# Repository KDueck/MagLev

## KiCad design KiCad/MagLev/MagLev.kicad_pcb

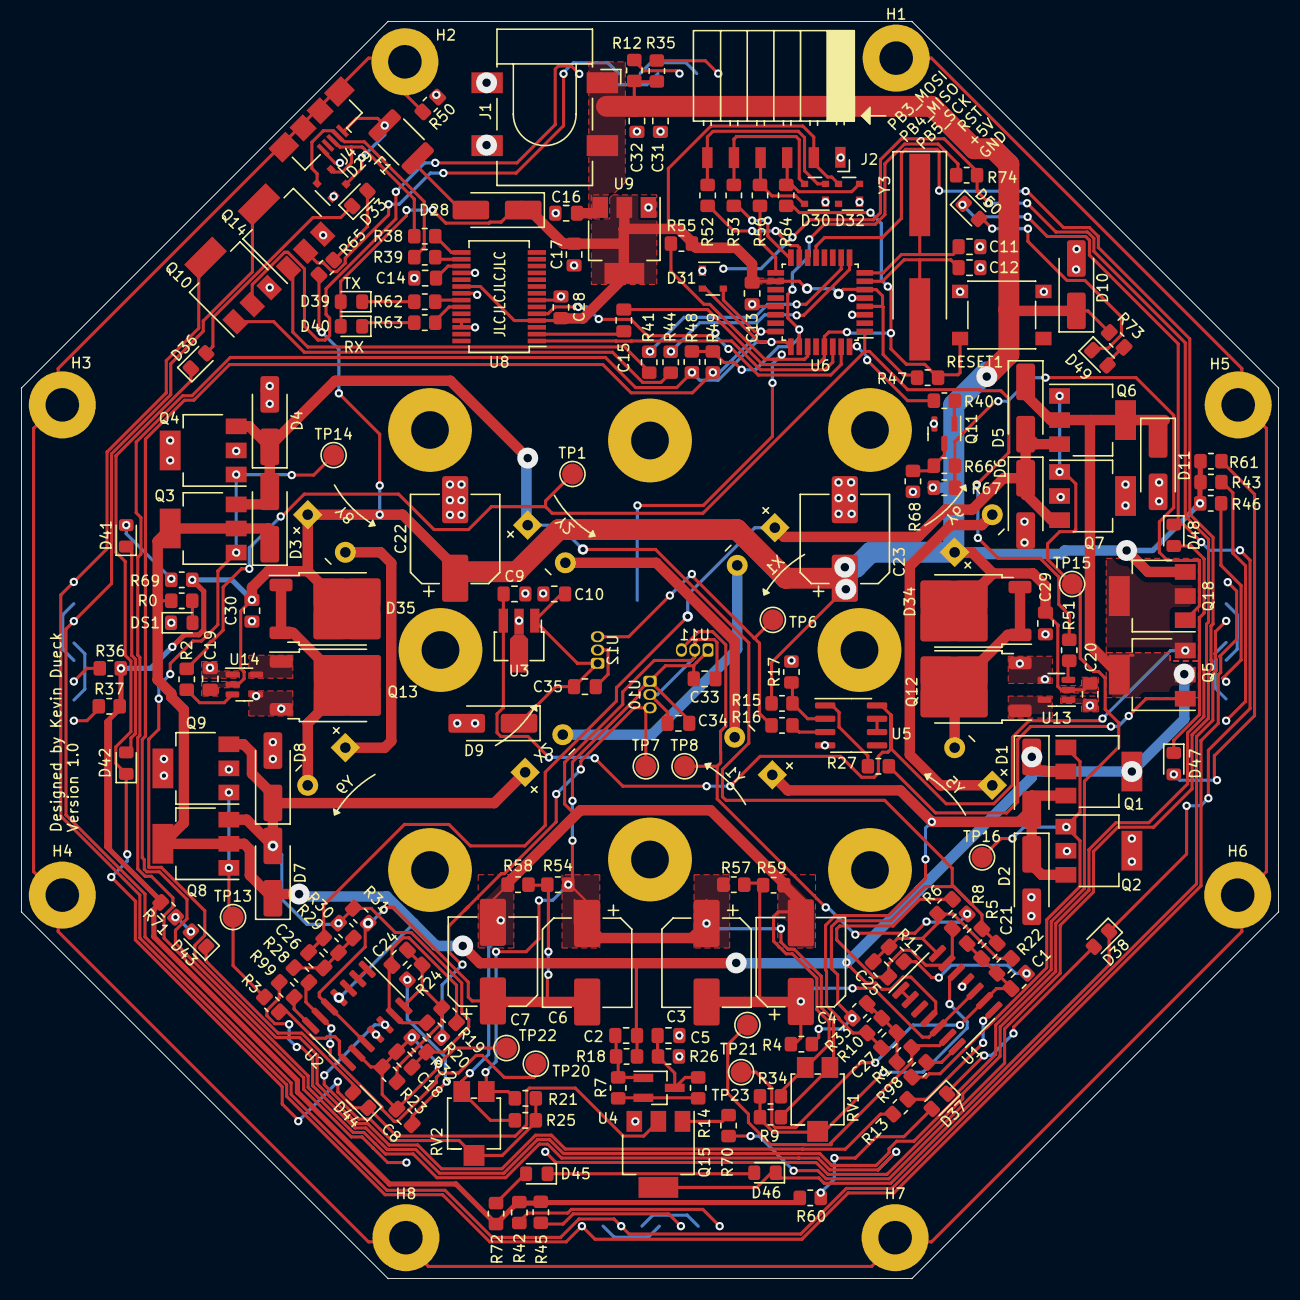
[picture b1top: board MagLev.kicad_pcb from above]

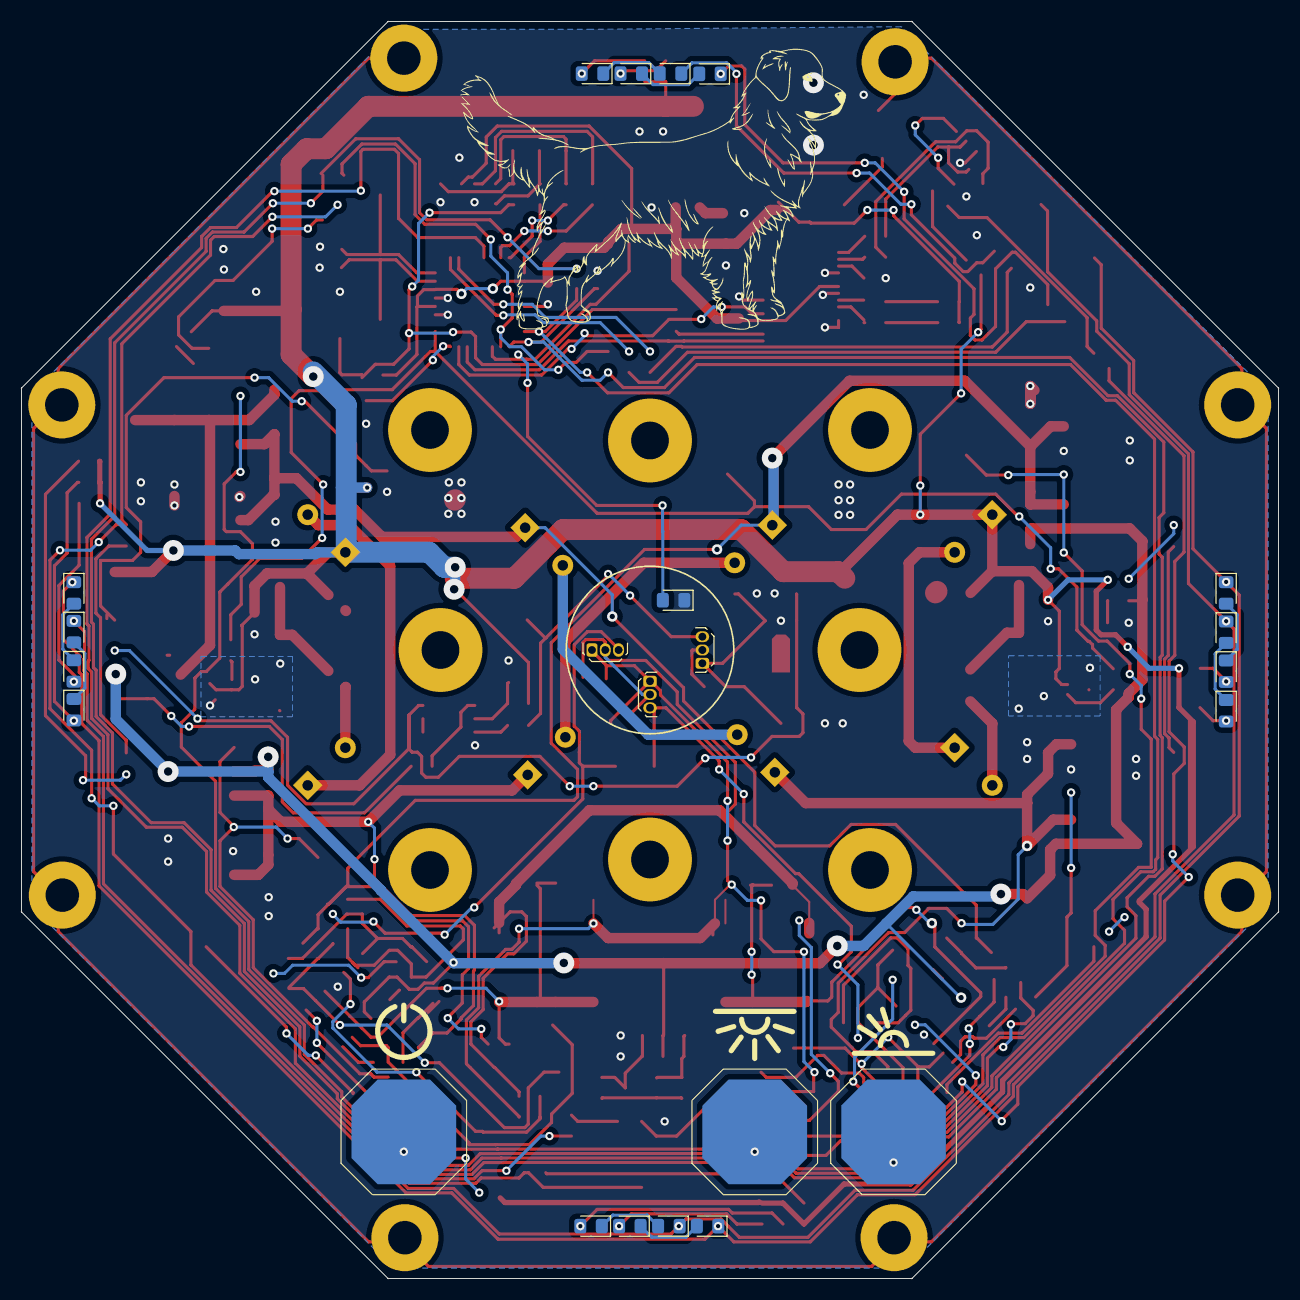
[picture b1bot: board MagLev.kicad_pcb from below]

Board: 2 copper layers, 120.0 x 120.0 mm, 232 parts (31 on the bottom side), 134 nets.

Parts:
C1, C8: 1uF; C_0805_2012Metric_Pad1.18x1.45mm_HandSolder
C2, C5: .1uF; C_0805_2012Metric_Pad1.18x1.45mm_HandSolder
C3, C4, C6, C7, C22, C23: 220uF; CP_Elec_8x10_HandSolder
C9: 0.33uF; C_0805_2012Metric_Pad1.18x1.45mm_HandSolder
C10: 0.01uF; C_0805_2012Metric_Pad1.18x1.45mm_HandSolder
C11, C12: 22pF; C_0805_2012Metric_Pad1.18x1.45mm_HandSolder
C13, C19, C20, C28, C32, C33, C34, C35: 0.1uF; C_0805_2012Metric_Pad1.18x1.45mm_HandSolder
C14, C15: 100nF; C_0805_2012Metric_Pad1.18x1.45mm_HandSolder
C16, C17: 10uF; C_0805_2012Metric_Pad1.18x1.45mm_HandSolder
C18, C21: 4.7nF; C_0805_2012Metric_Pad1.18x1.45mm_HandSolder
C24, C25: 470pF; C_0805_2012Metric_Pad1.18x1.45mm_HandSolder
C26, C27: 33nF; C_0805_2012Metric_Pad1.18x1.45mm_HandSolder
C29, C30, C31: 4.7uF; C_0805_2012Metric_Pad1.18x1.45mm_HandSolder
D1, D2, D3, D4, D5, D6, D7, D8: B140; D_SMA_Handsoldering
D9: SMAJ5.0A; D_SMA_Handsoldering
D10, D11: SMAJ12A; D_SMA_Handsoldering
D12, D13, D14, D15, D16, D17, D18, D19: WH; LED_0805_2012Metric_Pad1.15x1.40mm_HandSolder
D20, D21, D22, D23, D24, D25, D26, D27: UV; LED_0805_2012Metric_Pad1.15x1.40mm_HandSolder
D28: D; D_SMA_Handsoldering
D29, D30, D31, D32: SP0503BAHT; SOT-143
D33, D36, D37, D38, D41, D42, D43, D44, D45, D46, D47, D48, D49, D50: WRM; LED_0805_2012Metric_Pad1.15x1.40mm_HandSolder
D34, D35: MBRD1060; TO-252-Schottkey
D39: GREEN; LED_0805_2012Metric_Pad1.15x1.40mm_HandSolder
D40: Red; LED_0805_2012Metric_Pad1.15x1.40mm_HandSolder
DS1: GREEN; LED_0805_2012Metric_Pad1.15x1.40mm_HandSolder
F1: MF-MSMF050-2; Fuse_1812_4532Metric_Pad1.30x3.40mm_HandSolder
H1, H2, H3, H4, H5, H6, H7, H8: MountingHole_Pad; MountingHole_3.2mm_M3_Pad
J1: FC681465S; BarrelJack_CLIFF_FC681465S_SMT_Horizontal_No_Holes
J2: Programming header; PinSocket_1x06_P2.54mm_Horizontal_SM
J4: USB_B_Micro; USB_Micro-B_Amphenol_10104110_Horizontal_Overhang
PB1, PB2, PB3: Capacitive_Touch_Pad
Q1, Q3, Q6, Q8, Q10, Q14, Q15: ZX5T851GTA; SOT-223-3_TabPin2_BJT
Q2, Q4, Q5, Q7, Q9, Q18: ZX5T1951GTA; SOT-223-3_TabPin2_BJT
Q11: MMBT3904; SOT-23
Q12, Q13: AOD442G; TO-252-2
Q16: TEMT7000X01; LED_0805_2012Metric_Pad1.15x1.40mm_HandSolder
R0: 1K; R_0805_2012Metric_Pad1.20x1.40mm_HandSolder
R1, R28: 430k; R_0805_2012Metric_Pad1.20x1.40mm_HandSolder
R2, R9, R11, R21, R24, R25, R27, R34, R38, R39, R40, R41, R44, R47, R51, R52, R53, R54, R56, R57, R58, R59, R64, R66, R70: 1k; R_0805_2012Metric_Pad1.20x1.40mm_HandSolder
R3, R13, R98, R99: 51; R_0805_2012Metric_Pad1.20x1.40mm_HandSolder
R4, R31: 330k; R_0805_2012Metric_Pad1.20x1.40mm_HandSolder
R5, R8, R20, R32, R67: 10k; R_0805_2012Metric_Pad1.20x1.40mm_HandSolder
R6, R19: 130k; R_0805_2012Metric_Pad1.20x1.40mm_HandSolder
R7, R14, R16, R17: 5.1k; R_0805_2012Metric_Pad1.20x1.40mm_HandSolder
R10, R29: 1.5k; R_0805_2012Metric_Pad1.20x1.40mm_HandSolder
R12, R35, R36, R37, R42, R43, R45, R46, R60, R61, R65, R69, R71, R72, R73: 270; R_0805_2012Metric_Pad1.20x1.40mm_HandSolder
R15: 20k; R_0805_2012Metric_Pad1.20x1.40mm_HandSolder
R18, R26: 180; R_0805_2012Metric_Pad1.20x1.40mm_HandSolder
R22, R23: 3.3k; R_0805_2012Metric_Pad1.20x1.40mm_HandSolder
R30, R33: 1.2k; R_0805_2012Metric_Pad1.20x1.40mm_HandSolder
R48, R49, R50, R74: 1M; R_0805_2012Metric_Pad1.20x1.40mm_HandSolder
R55: 5k; R_0805_2012Metric_Pad1.20x1.40mm_HandSolder
R62, R63: 300; R_0805_2012Metric_Pad1.20x1.40mm_HandSolder
R68: 0; R_0805_2012Metric_Pad1.20x1.40mm_HandSolder
RESET1: PTS645; SW_SPST_PTS645
RV1, RV2: 1k; Potentiometer_ST-4EB
TP1: CoilPWM; TestPoint_Pad_D2.0mm
TP6: Hz; TestPoint_Pad_D2.0mm
TP7: Hx; TestPoint_Pad_D2.0mm
TP8: Hy; TestPoint_Pad_D2.0mm
TP13, TP14: Gx; TestPoint_Pad_D2.0mm
TP15, TP16: Gy; TestPoint_Pad_D2.0mm
TP20, TP21: Yin; TestPoint_Pad_D2.0mm
TP22, TP23: Xin; TestPoint_Pad_D2.0mm
U1, U2: LM324; SOIC-14_3.9x8.7mm_P1.27mm
U3: L78L05_SO8; SOT-89-3_Handsoldering_Vref
U4: TL431A; SOT-23_Handsoldering
U5: LM393; SOIC-8_3.9x4.9mm_P1.27mm
U6: ATmega328P-A; TQFP-32_7x7mm_P0.8mm
U8: FT232RL; SSOP-28_5.3x10.2mm_P0.65mm
U9: LM1117MP-5.0; SOT-223-3_TabPin2
U10, U11: DRV5505; TO-92Flat
U12: locked; TO-92Flat
U13, U14: MCP1402; SOT-23-5
X1, X2: L_Ferrite; Maglev_coil
Y1, Y2, Y5, Y6, Y8, Y9: L_Ferrite; Maglev_coil
Y3: J49SMH-16MHz; Crystal_SMD_HC49-SD_HandSoldering

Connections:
+5V: C13.1, C17.1, C28.1, D28.1 (K), D32.3 (K), D39.2 (A), D40.2 (A), J2.2, R47.2, R55.1, U6.4 (VCC), U6.6 (VCC), U6.18 (AVCC), U8.4 (VCCIO), U8.20 (VCC), U9.2 (VO)
/CoilPWM: R2.1, R51.1, TP1.1, U6.1 (PD3)
/DR: C2.1, D1.1 (K), D3.1 (K), D5.1 (K), D7.1 (K), D11.1 (A1), Q1.1 (C), Q3.1 (C), Q5.1 (C), Q6.1 (C), Q8.1 (C), R0.1, R18.2, U1.4 (V+), U2.4 (V+)
/En_sig: R40.2, U6.32 (PD2)
/H1: R8.2, TP8.1, U11.3 (OUTPUT)
/H2: R20.2, TP7.1, U10.3 (OUTPUT)
/MCU/LED_UV: R41.2, U6.10 (PD6)
/MCU/LED_WH: R44.2, U6.9 (PD5)
/MCU/LED_bot: R70.2, U6.13 (PB1)
/MCU/LightSense: Q16.2 (C), R55.2, U6.27 (PC4)
/MCU/PB3_MOSI: R52.1, U6.15 (PB3)
/MCU/PB4_MISO: R53.1, U6.16 (PB4)
/MCU/PB5_SCK: R56.1, U6.17 (PB5)
/MCU/RESET: C15.1, R47.1, R64.1, RESET1.1, U6.29 (~RESET/PC6)
/MCU/RXD0: U6.30 (PD0), U8.1 (TXD)
/MCU/TXD0: U6.31 (PD1), U8.5 (RXD)
/MCU/Touch1: D31.2 (K), PB1.1 (Out), R48.1, U6.25 (PC2)
/MCU/Touch2: D31.3 (K), PB2.1 (Out), R49.1, U6.24 (PC1)
/MCU/Touch3: D31.4 (K), PB3.1 (Out), R74.1
/MCU/TouchCom: R48.2, R49.2, R74.2, U6.26 (PC3)
/Vcc_en: C9.1, Q5.3 (E), Q18.1 (C), U3.3 (IN), U5.8 (V+)
/Vref+: C3.1, C6.1, C33.1, C34.1, R9.2, R21.2, R54.1, R57.1, RV1.3, RV2.3, U10.1 (VDD), U11.1 (VDD)
/Vref-: C4.2, C7.2, C33.2, C34.2, R25.2, R34.2, R58.2, R59.2, RV1.1, RV2.1, U10.2 (GND), U11.2 (GND)
/Vreg: C10.1, C35.1, D9.1 (A1), U3.1 (OUT), U12.1 (VDD)
/X1: C21.1, D3.2 (A), D4.1 (K), Q3.3 (E), Q4.3 (E), R4.2, R5.2, R33.2, Y2.1
/X2: C18.1, D7.2 (A), D8.1 (K), Q8.3 (E), Q9.3 (E), R30.2, R31.2, R32.2, X2.1
/Y1: C27.1, D1.2 (A), D2.1 (K), Q1.3 (E), Q2.3 (E), R10.1, Y1.1
/Y2: C26.1, D5.2 (A), D6.1 (K), Q6.3 (E), Q7.3 (E), R29.1, X1.1
Earth: H1.1, H2.1, H3.1, H4.1, H5.1, H6.1, H7.1, H8.1, J4.6 (Shield), R50.2
GND: C5.2, C9.2, C10.2, C11.2, C12.2, C13.2, C14.2, C16.2, C17.2, C19.2, C20.2, C22.2, C23.2, C28.2, C29.2, C30.2, C31.2, C32.2, C35.2, D2.2 (A), D4.2 (A), D6.2 (A), D8.2 (A), D9.2 (A2), D10.2 (A2), D11.2 (A2), D29.1 (A), D30.1 (A), D31.1 (A), D32.1 (A), DS1.1 (K), J1.2, J1.3, J2.1, J4.5 (GND), Q2.1 (C), Q4.1 (C), Q7.1 (C), Q9.1 (C), Q10.3 (E), Q11.2 (E), Q12.3 (S), Q13.3 (S), Q14.3 (E), Q15.3 (E), Q16.1 (E), R17.2, R26.1, R50.1, R68.2, RESET1.2, U1.11 (V-), U2.11 (V-), U3.2 (GND), U5.4 (V-), U6.3 (GND), U6.5 (GND), U6.21 (GND), U8.7 (GND), U8.18 (GND), U8.21 (GND), U8.25 (AGND), U8.26 (TEST), U9.1 (GND), U12.2 (GND), U13.1 (GND), U13.4 (GND), U14.1 (GND), U14.4 (GND)
unnamed: C1.1, R11.1
unnamed: C8.1, R24.1
unnamed: C24.1, R19.1, R23.2, R24.2, U2.14
unnamed: C25.1, R6.1, R11.2, R22.2, U1.14
unnamed: C26.2, R28.1, R29.2, R30.1
unnamed: C27.2, R1.1, R10.2, R33.1
unnamed: D12.2 (A), R12.1
unnamed: D12.1 (K), D13.2 (A)
unnamed: D13.1 (K), D15.1 (K), D17.1 (K), D19.1 (K), Q10.1 (C)
unnamed: D14.2 (A), R36.1
unnamed: D14.1 (K), D15.2 (A)
unnamed: D16.2 (A), R45.1
unnamed: D16.1 (K), D17.2 (A)
unnamed: D18.2 (A), R46.1
unnamed: D18.1 (K), D19.2 (A)
unnamed: D20.2 (A), R35.1
unnamed: D20.1 (K), D21.2 (A)
unnamed: D21.1 (K), D23.1 (K), D25.1 (K), D27.1 (K), Q14.1 (C)
unnamed: D22.2 (A), R37.1
unnamed: D22.1 (K), D23.2 (A)
unnamed: D24.2 (A), R42.1
unnamed: D24.1 (K), D25.2 (A)
unnamed: D26.2 (A), R43.1
unnamed: D26.1 (K), D27.2 (A)
unnamed: D28.2 (A), F1.1
unnamed: D33.2 (A), R65.1
unnamed: D33.1 (K), D36.2 (A)
unnamed: D34.2 (A), Q12.2 (D), Y5.2
unnamed: D35.2 (A), Q13.2 (D), Y9.2
unnamed: D36.1 (K), D38.1 (K), D42.1 (K), D44.1 (K), D46.1 (K), D48.1 (K), D50.1 (K), Q15.1 (C)
unnamed: D37.2 (A), R60.1
unnamed: D37.1 (K), D38.2 (A)
unnamed: D39.1 (K), R62.1
unnamed: D40.1 (K), R63.1
unnamed: D41.2 (A), R69.1
unnamed: D41.1 (K), D42.2 (A)
unnamed: D43.2 (A), R71.1
unnamed: D43.1 (K), D44.2 (A)
unnamed: D45.2 (A), R72.1
unnamed: D45.1 (K), D46.2 (A)
unnamed: D47.2 (A), R61.1
unnamed: D47.1 (K), D48.2 (A)
unnamed: D49.2 (A), R73.1
unnamed: D49.1 (K), D50.2 (A)
unnamed: DS1.2 (A), R0.2
unnamed: D32.2 (K), J2.3, R64.2
unnamed: D30.4 (K), J2.4, R56.2
unnamed: D30.3 (K), J2.5, R53.2
unnamed: D30.2 (K), J2.6, R52.2
unnamed: D29.3 (K), J4.3 (D+), R38.1
unnamed: D29.4 (K), J4.2 (D-), R39.2
unnamed: D29.2 (K), F1.2, J4.1 (VBUS)
unnamed: Q1.2 (B), Q2.2 (B), R98.1, TP16.1
unnamed: Q3.2 (B), Q4.2 (B), R13.1, TP14.1
unnamed: Q5.2 (B), R27.2
unnamed: Q6.2 (B), Q7.2 (B), R99.1, TP15.1
unnamed: Q8.2 (B), Q9.2 (B), R3.1, TP13.1
unnamed: Q10.2 (B), R44.1
unnamed: Q11.1 (B), R40.1
unnamed: Q11.3 (C), R66.2, R68.1
unnamed: Q12.1 (G), U13.5 (OUT)
unnamed: Q13.1 (G), U14.5 (OUT)
unnamed: Q14.2 (B), R41.1
unnamed: Q15.2 (B), R70.1
unnamed: Q18.2 (B), R66.1, R67.1
unnamed: R3.2, U2.8
unnamed: R13.2, U1.8
unnamed: R27.1, U5.1
unnamed: R98.2, U1.7
unnamed: R99.2, U2.7
unnamed: U1.1, U1.2 (-)
unnamed: C3.2, C4.1, R4.1, R57.2, R59.1, U1.5 (+), U1.10 (+)
unnamed: R1.2, TP21.1, U1.6 (-)
unnamed: C1.2, C21.2, R5.1, R22.1, TP23.1, U1.9 (-)
unnamed: R9.1, R34.1, RV1.2, U1.12 (+)
unnamed: C25.2, R6.2, R8.1, U1.13 (-)
unnamed: U2.1, U2.2 (-)
unnamed: C6.2, C7.1, R31.1, R54.2, R58.1, U2.5 (+), U2.10 (+)
unnamed: R28.2, TP20.1, U2.6 (-)
unnamed: C8.2, C18.2, R23.1, R32.1, TP22.1, U2.9 (-)
unnamed: R21.1, R25.1, RV2.2, U2.12 (+)
unnamed: C24.2, R19.2, R20.1, U2.13 (-)
unnamed: C5.1, R14.2, R26.2, U4.3 (A)
unnamed: C2.2, R7.2, R18.1, U4.1 (C)
unnamed: R7.1, R14.1, U4.2 (Ref)
unnamed: R16.1, U5.3 (+)
unnamed: R15.2, R17.1, U5.2 (-)
unnamed: U5.6 (-), U5.7
unnamed: C12.1, U6.7 (XTAL1/PB6), Y3.2
unnamed: C11.1, U6.8 (XTAL2/PB7), Y3.1
unnamed: C14.1, U8.17 (3V3OUT)
unnamed: R63.2, U8.23 (CBUS0)
unnamed: R62.2, U8.22 (CBUS1)
unnamed: C15.2, U8.2 (DTR)
unnamed: R38.2, U8.15 (USBD+)
unnamed: R39.1, U8.16 (USBD-)
unnamed: R16.2, TP6.1, U12.3 (OUTPUT)
unnamed: R51.2, U13.3 (IN)
unnamed: R2.2, U14.3 (IN)
unnamed: X1.2, X2.2
unnamed: Y1.2, Y2.2
unnamed: Y5.1, Y6.2
unnamed: Y8.2, Y9.1
VCC: C16.1, C19.1, C20.1, C22.1, C23.1, C29.1, C30.1, C31.1, C32.1, D10.1 (A1), D34.1 (K), D35.1 (K), J1.1, Q18.3 (E), R12.2, R15.1, R35.2, R36.2, R37.2, R42.2, R43.2, R45.2, R46.2, R60.2, R61.2, R65.2, R67.2, R69.2, R71.2, R72.2, R73.2, U9.3 (VI), U13.2 (Vdd), U14.2 (Vdd), Y6.1, Y8.1

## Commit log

2023-08-05 Initial commit.
2023-08-05 Start schematic, add hierarchical sheet.
2023-08-05 Update component names to match ENB schematic.
2023-08-05 Complete schematic equivilant to ENBs.
2023-08-06 Clean up schematics, add title block info.
2023-08-06 Add footprints to all components, add datasheet directory.
2023-08-06 Update spice model to match enbs design. Add TVS diodes to schematic.
2023-08-07 Add MCU page to schematic.
2023-08-07 Add MCU and FTDI IC to schematic.
2023-08-07 Add power fets and additional coils to schematic.
2023-08-08 Add MCU enable circuit and leds.
2023-08-08 Assign footprints to MCU components.
2023-08-08 Series coils, add TPs.
2023-08-08 Add netclasses, define PCB rules.
2023-08-09 Place and route MCU page components.
2023-08-09 Place and route X and Y amplifier components.
2023-08-10 Finish layout up to TPs.
2023-08-10 Route TPs, increase power trace size.
2023-08-10 Fix DRC errors.
2023-08-11 Add decoupling caps to PWM switching Fets.
2023-08-11 Review all footprints.
2023-08-11 Set LED bias resistors. Move MCU status LEDs to PWM pins.
2023-08-11 Generate output files.
2023-08-11 Version 1.0 release.
2023-08-12 Remove silkscreen components from back layer. Cleanup schematic and pcb.
2023-08-12 Move op-amps further into board.
2023-08-12 Add underglow.
2023-08-13 Update LED PCB reference after adding new LED schematic sheet.
2023-08-13 Update BOM with JLCPCB PNs.
2023-08-13 Add some PCB art.
2023-08-28 Add board art folder and upload svg files.
2023-10-06 Add board art, one layer.
2023-10-06 Create project outputs for order, cleanup BOM.
